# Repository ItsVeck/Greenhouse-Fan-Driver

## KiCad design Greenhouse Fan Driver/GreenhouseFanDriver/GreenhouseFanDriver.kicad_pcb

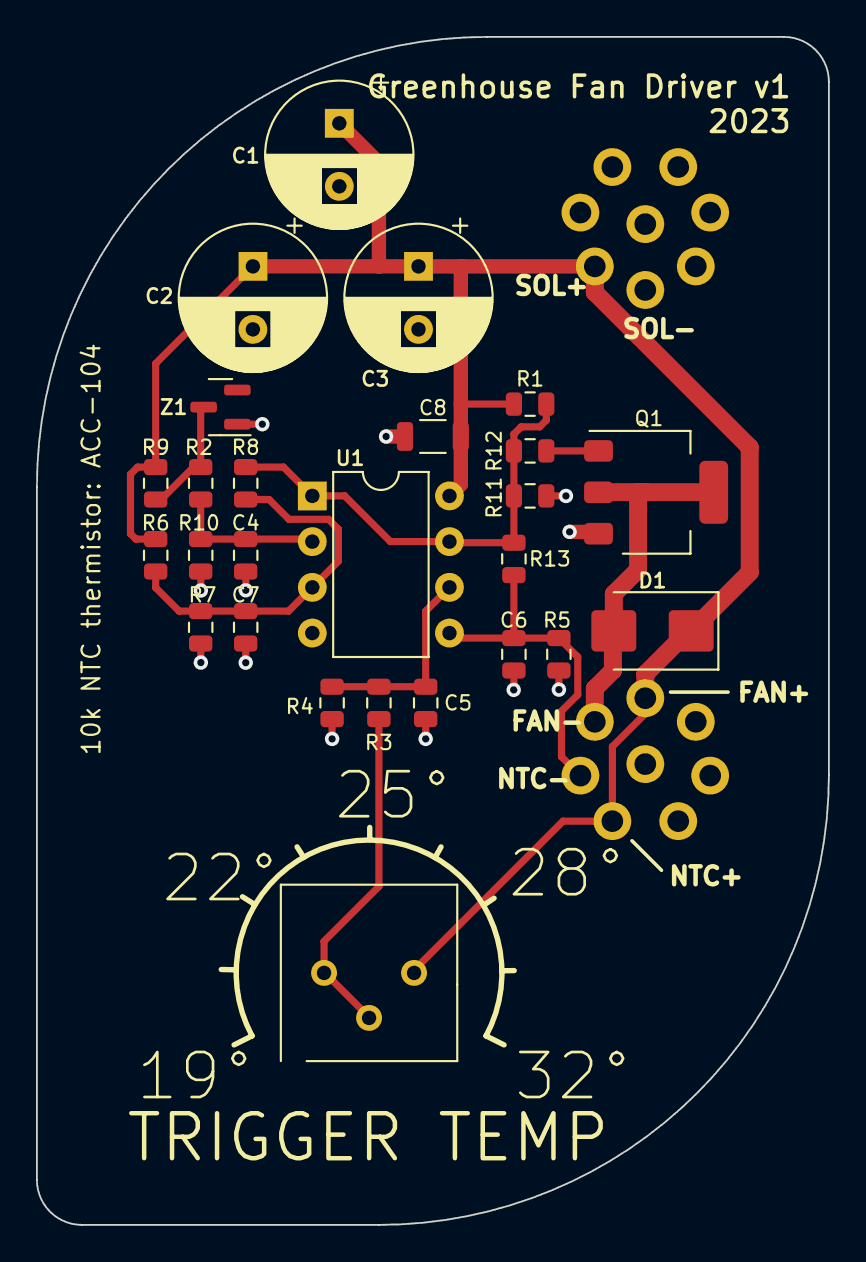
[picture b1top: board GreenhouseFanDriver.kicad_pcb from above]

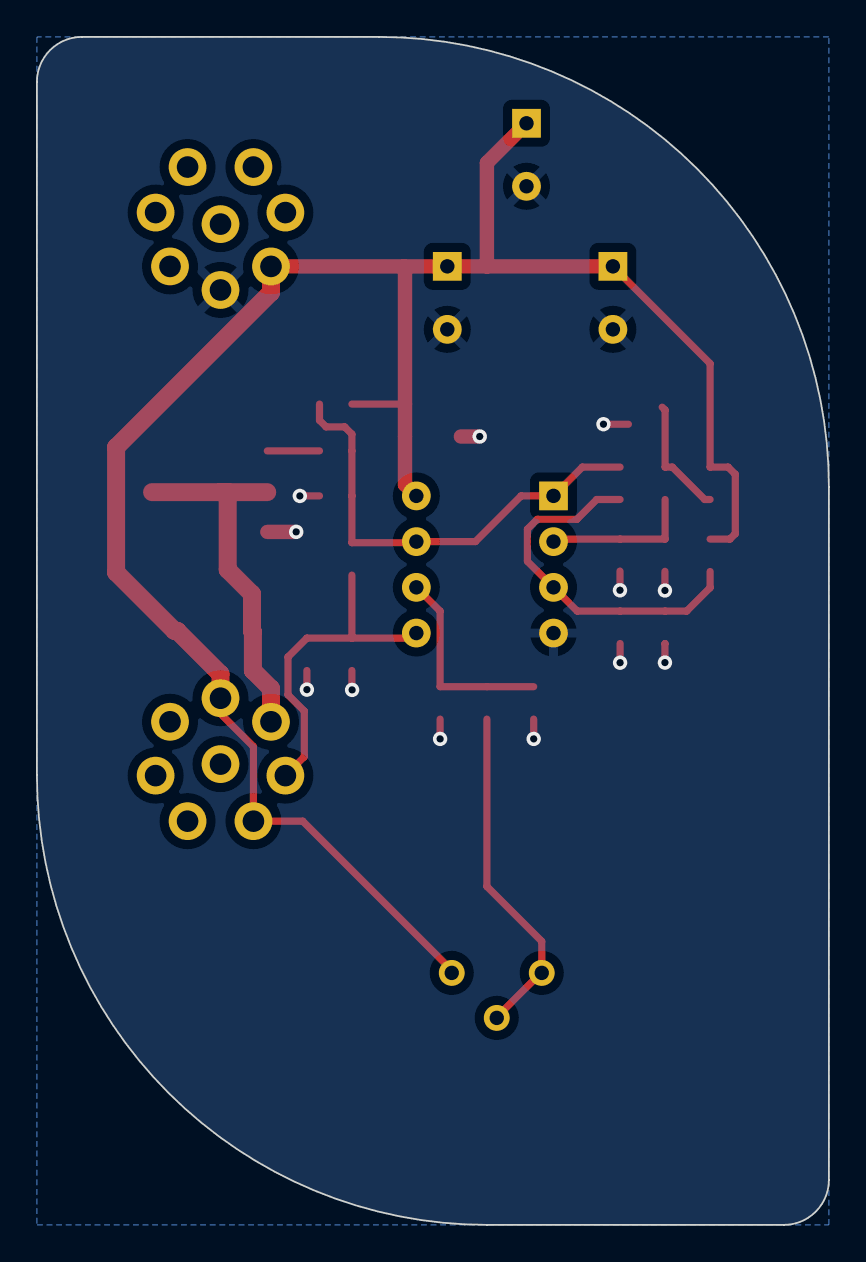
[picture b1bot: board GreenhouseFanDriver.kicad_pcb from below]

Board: 2 copper layers, 44.0 x 66.0 mm, 28 parts (2 on the bottom side), 11 nets.

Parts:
C1, C2, C3: 100uF; CP_Radial_D8.0mm_P3.50mm
C4, C5, C6, C7: 100n; C_0805_2012Metric_Custom
C8: 100n C0G; C_1206_3216Metric_Custom
D1: SS110B; D_SMB
J1: Fan/NTC; ODS_CCBPM08MCC
J2: Solar Panel; ODS_CCBPM08MCC
Q1: DMN6075S; SOT-223_Custom_DiodesIncorporated
R1, R3, R10: 47k; C_0805_2012Metric_Custom
R2, R11: 33k; C_0805_2012Metric_Custom
R4: 100k; C_0805_2012Metric_Custom
R5: 12k; C_0805_2012Metric_Custom
R6: 91k; C_0805_2012Metric_Custom
R7: 130k; C_0805_2012Metric_Custom
R8: 470k; C_0805_2012Metric_Custom
R9: 2k; C_0805_2012Metric_Custom
R12: 20R; C_0805_2012Metric_Custom
R13: 220k; C_0805_2012Metric_Custom
RV1: B100k; Potentiometer_Trimmer_72PTR100KLF_Custom
U1: LM393; DIP-8_W7.62mm
Z1: BZX84B18LT1G (18V); SOT-23

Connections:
+SOL: C1.1, C2.1, C3.1, C8.1, D1.1 (K), J1.1, J1.4, J2.5, R1.1, R6.1, R9.1, RV1.3, U1.8 (V+)
/EN_V: C7.1, R6.2, R7.1, R8.1, U1.3 (+)
/EN_Vref: C4.1, R2.2, R10.1, U1.2 (-)
/EN_sig: R1.2, R8.2, R11.1, R12.1, R13.2, U1.1, U1.7
/FAN-: D1.2 (A), J1.3, Q1.3 (D)
/NTC-: C6.1, J1.2, R5.1, R13.1, U1.5 (+)
/Temp_Vref: C5.1, R3.2, R4.1, U1.6 (-)
GND: C1.2, C2.2, C3.2, C4.2, C5.2, C6.2, C7.2, C8.2, J2.4, Q1.2 (S), R4.2, R5.2, R7.2, R10.2, R11.2, U1.4 (V-), Z1.1 (A)
unnamed: Q1.1 (G), R12.2
unnamed: R3.1, RV1.1, RV1.2
unnamed: R2.1, R9.2, Z1.3 (K)
